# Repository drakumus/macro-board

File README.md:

# macro-board
 My pcb design for a macro board

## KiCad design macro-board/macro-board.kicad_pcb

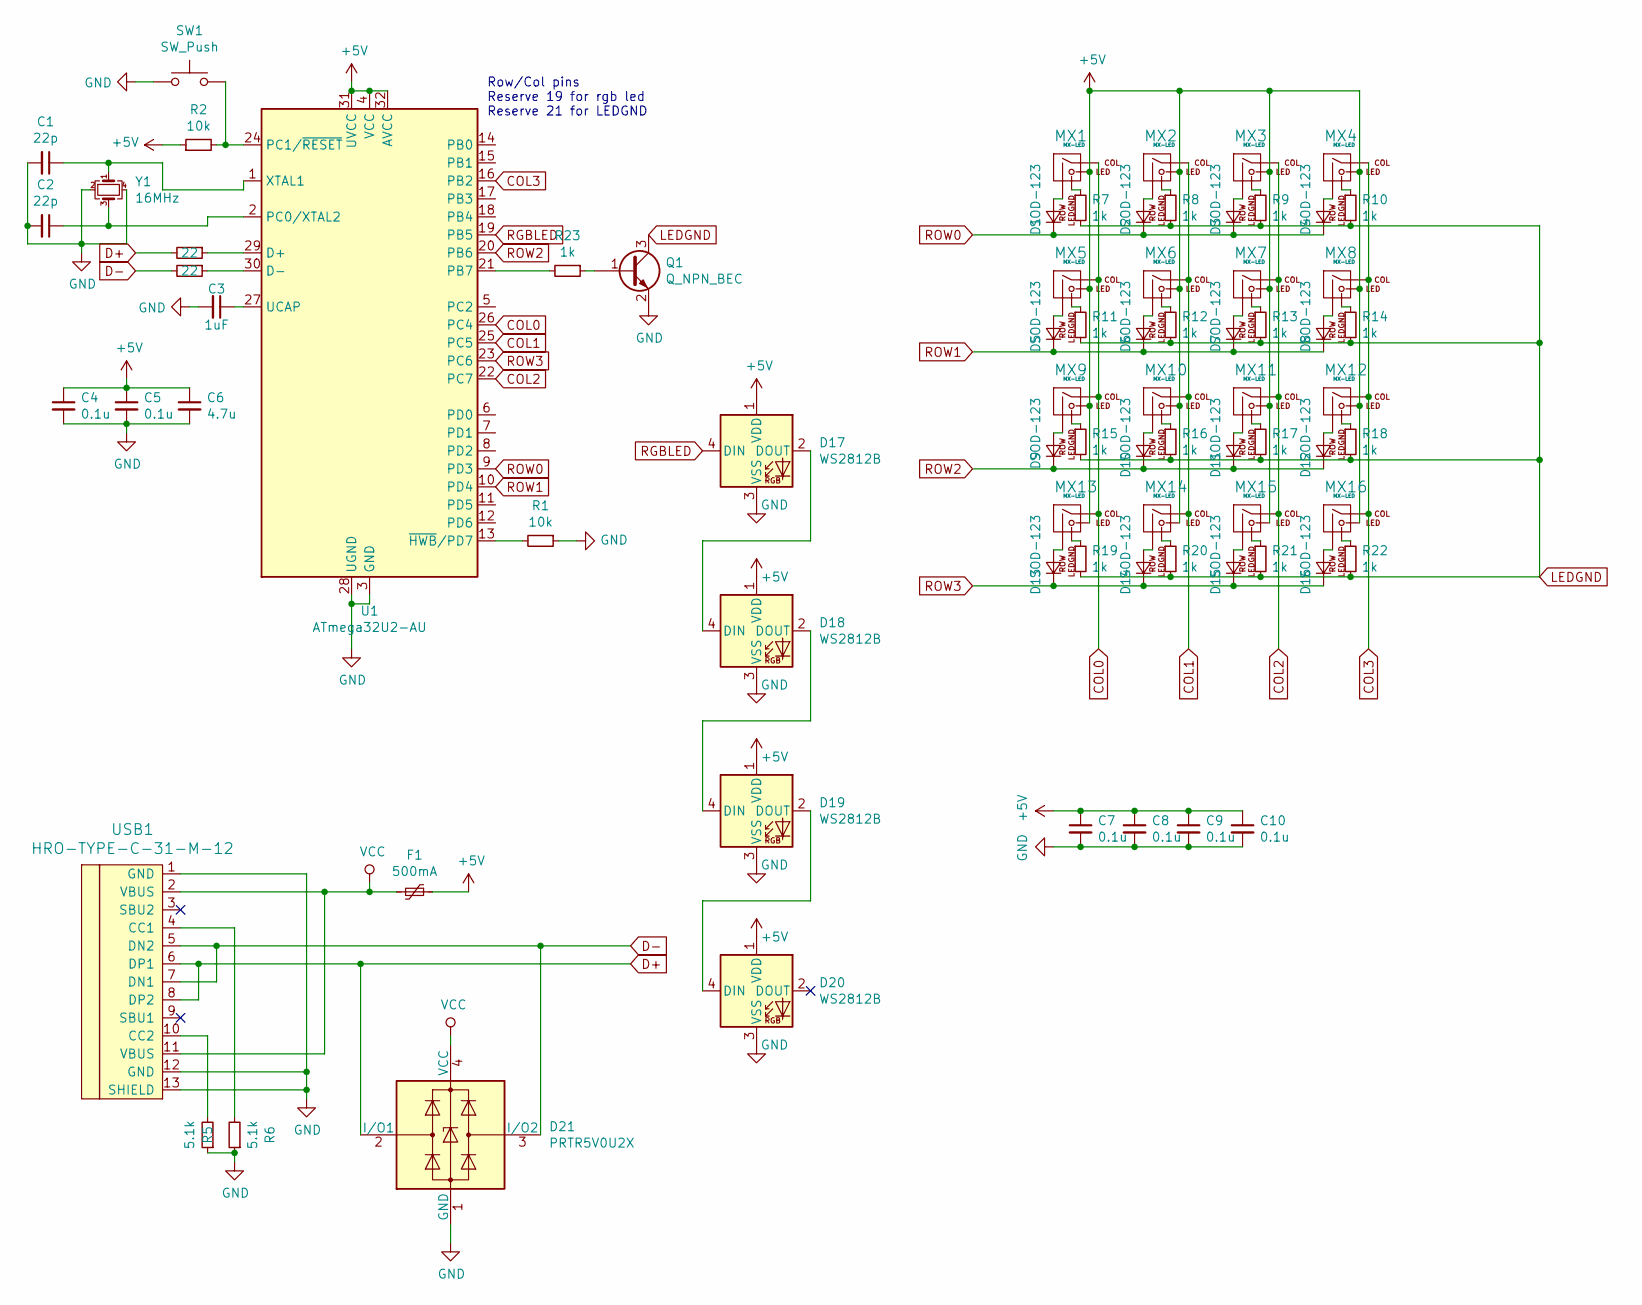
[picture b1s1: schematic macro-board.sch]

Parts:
C1, C2: 22p; C_0603_1608Metric
C3: 1uF; C_0603_1608Metric
C4, C5, C7, C8, C9, C10: 0.1u; C_0603_1608Metric
C6: 4.7u; C_0603_1608Metric
D1, D2, D3, D4, D5, D6, D7, D8, D9, D10, D11, D12, D13, D14, D15, D16: SOD-123; D_SOD-123
D17, D18, D19, D20: WS2812B; LED_WS2812B_PLCC4_5.0x5.0mm_P3.2mm
D21: PRTR5V0U2X; SOT143B
F1: 500mA; Fuse_1206_3216Metric
MX1, MX2, MX3, MX4, MX5, MX6, MX7, MX8, MX9, MX10, MX11, MX12, MX13, MX14, MX15, MX16: MX-LED; MX-1U
Q1: Q_NPN_BEC; SOT-23
R1, R2: 10k; R_0805_2012Metric
R3, R4: 22; R_0805_2012Metric
R5, R6: 5.1k; R_0805_2012Metric
R7, R8, R9, R10, R11, R12, R13, R14, R15, R16, R17, R18, R19, R20, R21, R22, R23: 1k; R_0805_2012Metric
SW1: SW_Push; SKQG-1155865
U1: ATmega32U2-AU; QFN-32-1EP_5x5mm_Pitch0.5mm
USB1: HRO-TYPE-C-31-M-12
Y1: 16MHz; Crystal_SMD_3225-4Pin_3.2x2.5mm

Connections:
+5V: C4.1, C5.1, C6.1, C7.1, C8.1, C9.1, C10.1, D17.1 (VDD), D18.1 (VDD), D19.1 (VDD), D20.1 (VDD), F1.1, MX1.3 (LED), MX2.3 (LED), MX3.3 (LED), MX4.3 (LED), MX5.3 (LED), MX6.3 (LED), MX7.3 (LED), MX8.3 (LED), MX9.3 (LED), MX10.3 (LED), MX11.3 (LED), MX12.3 (LED), MX13.3 (LED), MX14.3 (LED), MX15.3 (LED), MX16.3 (LED), R2.1, U1.4 (VCC), U1.31 (UVCC), U1.32 (AVCC)
COL0: MX1.1 (COL), MX5.1 (COL), MX9.1 (COL), MX13.1 (COL), U1.26 (PC4)
COL1: MX2.1 (COL), MX6.1 (COL), MX10.1 (COL), MX14.1 (COL), U1.25 (PC5)
COL2: MX3.1 (COL), MX7.1 (COL), MX11.1 (COL), MX15.1 (COL), U1.22 (PC7)
COL3: MX4.1 (COL), MX8.1 (COL), MX12.1 (COL), MX16.1 (COL), U1.16 (PB2)
D+: D21.2 (I/O1), R4.2, USB1.6 (DP1), USB1.8 (DP2)
D-: D21.3 (I/O2), R3.2, USB1.5 (DN2), USB1.7 (DN1)
GND: C1.2, C2.2, C3.2, C4.2, C5.2, C6.2, C7.2, C8.2, C9.2, C10.2, D17.3 (VSS), D18.3 (VSS), D19.3 (VSS), D20.3 (VSS), D21.1 (GND), Q1.2 (E), R1.1, R5.1, R6.1, SW1.1, U1.3 (GND), U1.28 (UGND), USB1.1 (GND), USB1.12 (GND), USB1.13 (SHIELD), Y1.2, Y1.4
LEDGND: Q1.3 (C), R7.2, R8.2, R9.2, R10.2, R11.2, R12.2, R13.2, R14.2, R15.2, R16.2, R17.2, R18.2, R19.2, R20.2, R21.2, R22.2
unnamed: C1.1, U1.1 (XTAL1), Y1.1
unnamed: C2.1, U1.2 (PC0/XTAL2), Y1.3
unnamed: C3.1, U1.27 (UCAP)
unnamed: D1.2 (A), MX1.2 (ROW)
unnamed: D2.2 (A), MX2.2 (ROW)
unnamed: D3.2 (A), MX3.2 (ROW)
unnamed: D4.2 (A), MX4.2 (ROW)
unnamed: D5.2 (A), MX5.2 (ROW)
unnamed: D6.2 (A), MX6.2 (ROW)
unnamed: D7.2 (A), MX7.2 (ROW)
unnamed: D8.2 (A), MX8.2 (ROW)
unnamed: D9.2 (A), MX9.2 (ROW)
unnamed: D10.2 (A), MX10.2 (ROW)
unnamed: D11.2 (A), MX11.2 (ROW)
unnamed: D12.2 (A), MX12.2 (ROW)
unnamed: D13.2 (A), MX13.2 (ROW)
unnamed: D14.2 (A), MX14.2 (ROW)
unnamed: D15.2 (A), MX15.2 (ROW)
unnamed: D16.2 (A), MX16.2 (ROW)
unnamed: D17.2 (DOUT), D18.4 (DIN)
unnamed: D18.2 (DOUT), D19.4 (DIN)
unnamed: D19.2 (DOUT), D20.4 (DIN)
unnamed: MX1.4 (LEDGND), R7.1
unnamed: MX2.4 (LEDGND), R8.1
unnamed: MX3.4 (LEDGND), R9.1
unnamed: MX4.4 (LEDGND), R10.1
unnamed: MX5.4 (LEDGND), R11.1
unnamed: MX6.4 (LEDGND), R12.1
unnamed: MX7.4 (LEDGND), R13.1
unnamed: MX8.4 (LEDGND), R14.1
unnamed: MX9.4 (LEDGND), R15.1
unnamed: MX10.4 (LEDGND), R16.1
unnamed: MX11.4 (LEDGND), R17.1
unnamed: MX12.4 (LEDGND), R18.1
unnamed: MX13.4 (LEDGND), R19.1
unnamed: MX14.4 (LEDGND), R20.1
unnamed: MX15.4 (LEDGND), R21.1
unnamed: MX16.4 (LEDGND), R22.1
unnamed: Q1.1 (B), R23.1
unnamed: R1.2, U1.13 (~HWB~/PD7)
unnamed: R2.2, SW1.2, U1.24 (PC1/~RESET)
unnamed: R3.1, U1.30 (D-)
unnamed: R4.1, U1.29 (D+)
unnamed: R5.2, USB1.10 (CC2)
unnamed: R6.2, USB1.4 (CC1)
unnamed: R23.2, U1.21 (PB7)
RGBLED: D17.4 (DIN), U1.19 (PB5)
ROW0: D1.1 (K), D2.1 (K), D3.1 (K), D4.1 (K), U1.9 (PD3)
ROW1: D5.1 (K), D6.1 (K), D7.1 (K), D8.1 (K), U1.10 (PD4)
ROW2: D9.1 (K), D10.1 (K), D11.1 (K), D12.1 (K), U1.20 (PB6)
ROW3: D13.1 (K), D14.1 (K), D15.1 (K), D16.1 (K), U1.23 (PC6)
VCC: D21.4 (VCC), F1.2, USB1.2 (VBUS), USB1.11 (VBUS)

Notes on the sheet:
Row/Col pins Reserve 19 for rgb led Reserve 21 for LEDGND

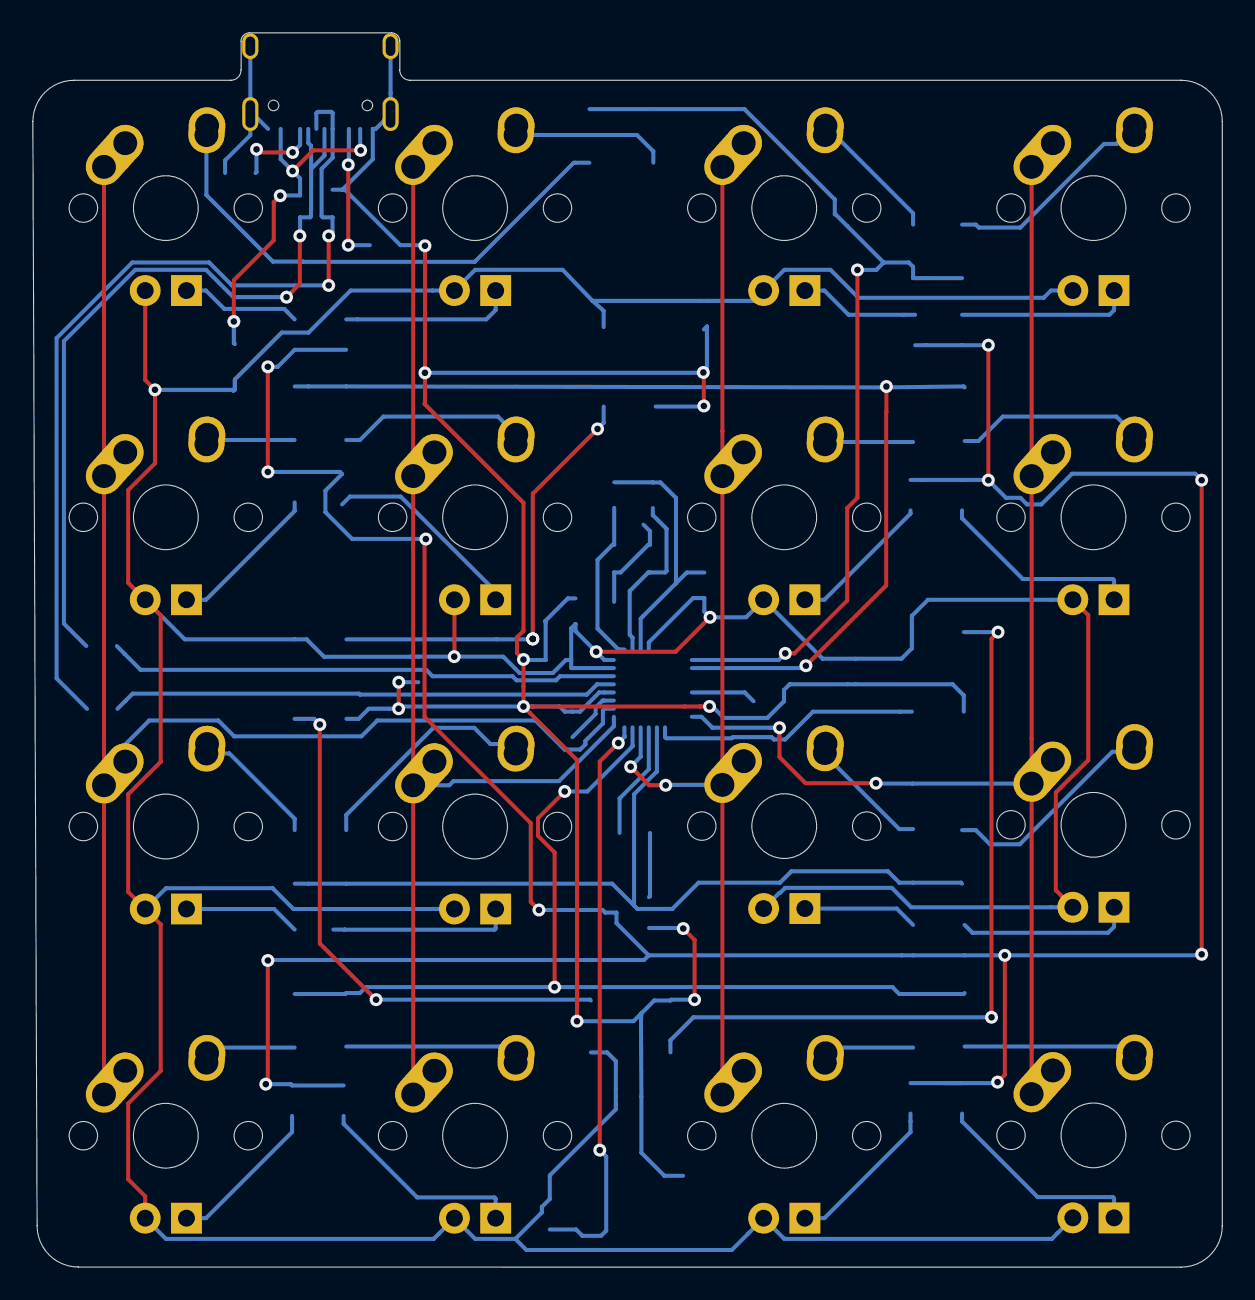
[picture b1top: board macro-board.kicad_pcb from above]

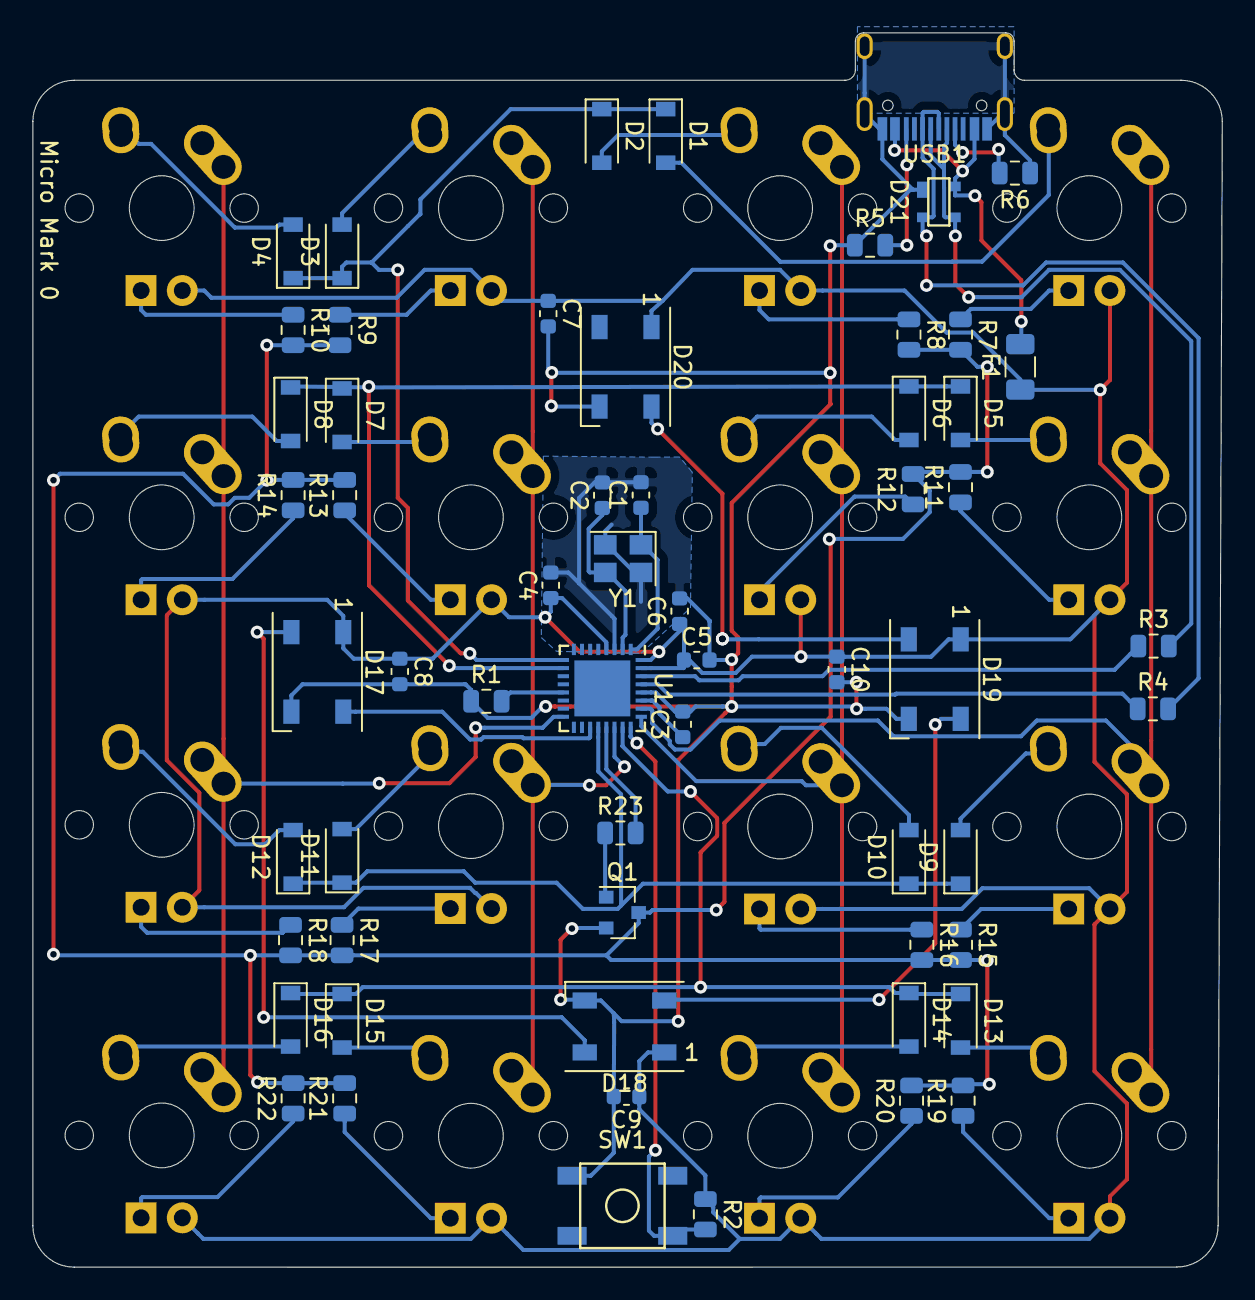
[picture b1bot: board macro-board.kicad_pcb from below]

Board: 2 copper layers, 73.3 x 76.0 mm, 76 parts (60 on the bottom side), 61 nets.

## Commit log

2020-02-29 progress on schematic
2020-02-29 basically finalize pcb
2020-02-29 changes before assigning footprint
2020-02-29 add footprint mapping
2020-02-29 start work on pcb routing
2020-02-29 routing pain
2020-03-01 finalize routing
